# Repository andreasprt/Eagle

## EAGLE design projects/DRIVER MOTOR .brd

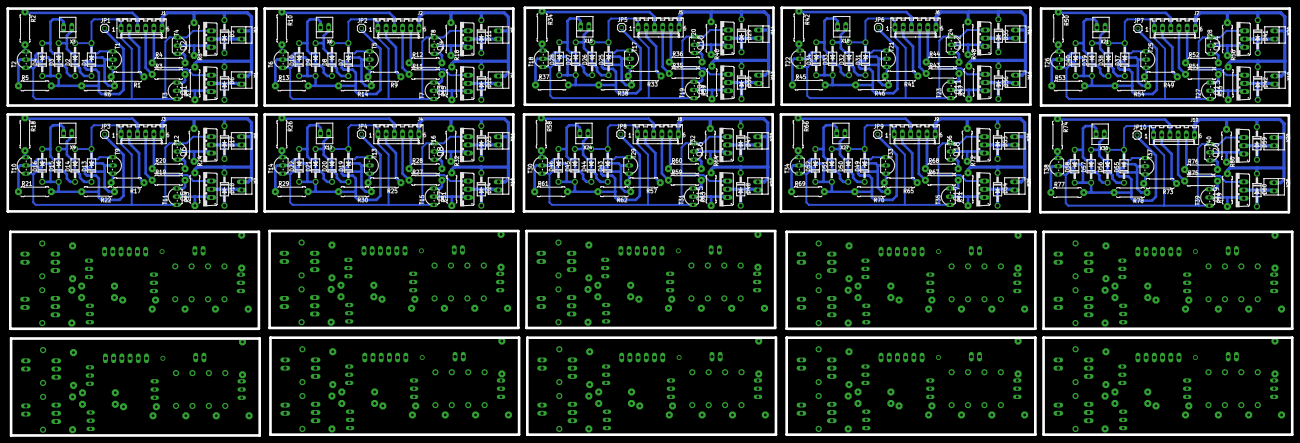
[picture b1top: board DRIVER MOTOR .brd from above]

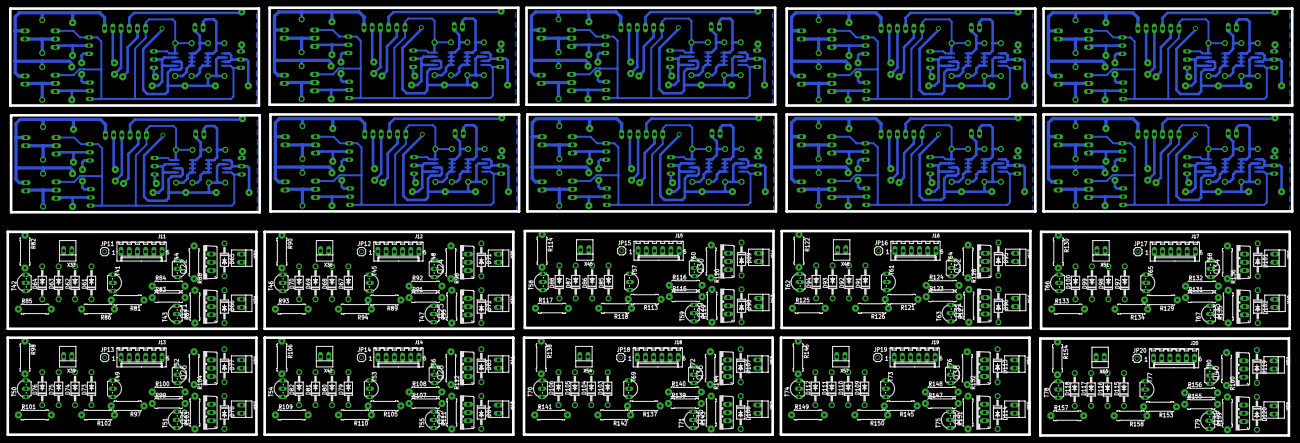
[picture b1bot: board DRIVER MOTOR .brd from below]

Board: 2 copper layers, 397.5 x 132.4 mm, 520 parts (270 on the bottom side), 190 nets.

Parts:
D1, D2, D3, D4, D5, D6, D7, D8, D9, D10, D11, D12, D13, D14, D15, D16, D17, D18, D19, D20, D21, D22, D23, D24, D25, D26, D27, D28, D29, D30, D31, D32, D33, D34, D35, D36, D37, D38, D39, D40, D41, D42, D43, D44, D45, D46, D47, D48, D49, D50, D51, D52, D53, D54, D55, D56, D57, D58, D59, D60, D61, D62, D63, D64, D65, D66, D67, D68, D69, D70, D71, D72, D73, D74, D75, D76, D77, D78, D79, D80, D81, D82, D83, D84, D85, D86, D87, D88, D89, D90, D91, D92, D93, D94, D95, D96, D97, D98, D99, D100, D101, D102, D103, D104, D105, D106, D107, D108, D109, D110, D111, D112, D113, D114, D115, D116, D117, D118, D119, D120: 1N4004; DO41-10
IC1, IC2, IC3, IC4, IC5, IC6, IC7, IC8, IC9, IC10, IC11, IC12, IC13, IC14, IC15, IC16, IC17, IC18, IC19, IC20: LM555D; SO08
J1, J2, J3, J4, J5, J6, J7, J8, J9, J10, J11, J12, J13, J14, J15, J16, J17, J18, J19, J20: 22-27-2061-06; 6410-06
JP1, JP2, JP3, JP4, JP5, JP6, JP7, JP8, JP9, JP10, JP11, JP12, JP13, JP14, JP15, JP16, JP17, JP18, JP19, JP20: 1X01
Q1, Q2, Q3, Q4, Q5, Q6, Q7, Q8, Q9, Q10, Q11, Q12, Q13, Q14, Q15, Q16, Q17, Q18, Q19, Q20, Q21, Q22, Q23, Q24, Q25, Q26, Q27, Q28, Q29, Q30, Q31, Q32, Q33, Q34, Q35, Q36, Q37, Q38, Q39, Q40: IRF530; TO220BV
R1, R2, R3, R4, R9, R10, R11, R12, R17, R18, R19, R20, R25, R26, R27, R28, R33, R34, R35, R36, R41, R42, R43, R44, R49, R50, R51, R52, R57, R58, R59, R60, R65, R66, R67, R68, R73, R74, R75, R76, R81, R82, R83, R84, R89, R90, R91, R92, R97, R98, R99, R100, R105, R106, R107, R108, R113, R114, R115, R116, R121, R122, R123, R124, R129, R130, R131, R132, R137, R138, R139, R140, R145, R146, R147, R148, R153, R154, R155, R156: 150K; 0309/10
R5, R6, R13, R14, R21, R22, R29, R30, R37, R38, R45, R46, R53, R54, R61, R62, R69, R70, R77, R78, R85, R86, R93, R94, R101, R102, R109, R110, R117, R118, R125, R126, R133, R134, R141, R142, R149, R150, R157, R158: 68K; 0309/10
R7, R8, R15, R16, R23, R24, R31, R32, R39, R40, R47, R48, R55, R56, R63, R64, R71, R72, R79, R80, R87, R88, R95, R96, R103, R104, R111, R112, R119, R120, R127, R128, R135, R136, R143, R144, R151, R152, R159, R160: 47K; 0309/10
T1, T2, T3, T4, T5, T6, T7, T8, T9, T10, T11, T12, T13, T14, T15, T16, T17, T18, T19, T20, T21, T22, T23, T24, T25, T26, T27, T28, T29, T30, T31, T32, T33, T34, T35, T36, T37, T38, T39, T40, T41, T42, T43, T44, T45, T46, T47, T48, T49, T50, T51, T52, T53, T54, T55, T56, T57, T58, T59, T60, T61, T62, T63, T64, T65, T66, T67, T68, T69, T70, T71, T72, T73, T74, T75, T76, T77, T78, T79, T80: 2SC945; TO92-ECB
X1, X2, X3, X4, X5, X6, X7, X8, X9, X10, X11, X12, X13, X14, X15, X16, X17, X18, X19, X20, X21, X22, X23, X24, X25, X26, X27, X28, X29, X30, X31, X32, X33, X34, X35, X36, X37, X38, X39, X40, X41, X42, X43, X44, X45, X46, X47, X48, X49, X50, X51, X52, X53, X54, X55, X56, X57, X58, X59, X60: 22-23-2021

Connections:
+12V: D3.C, D4.C, IC1.3, IC2.3, JP1.1, R5.2, R6.2
+12V1: D9.C, D10.C, IC3.3, IC4.3, JP2.1, R13.2, R14.2
+12V2: D15.C, D16.C, IC5.3, IC6.3, JP3.1, R21.2, R22.2
+12V3: D21.C, D22.C, IC7.3, IC8.3, JP4.1, R29.2, R30.2
+12V4: D27.C, D28.C, IC9.3, IC10.3, JP5.1, R37.2, R38.2
+12V5: D33.C, D34.C, IC11.3, IC12.3, JP6.1, R45.2, R46.2
+12V6: D39.C, D40.C, IC13.3, IC14.3, JP7.1, R53.2, R54.2
+12V7: D45.C, D46.C, IC15.3, IC16.3, JP8.1, R61.2, R62.2
+12V8: D51.C, D52.C, IC17.3, IC18.3, JP9.1, R69.2, R70.2
+12V9: D57.C, D58.C, IC19.3, IC20.3, JP10.1, R77.2, R78.2
GND: D1.A, D2.A, IC1.1, IC2.1, J1.1, Q1.S, Q2.S, T1.E, T2.E, T3.E, T4.E
GND1: D7.A, D8.A, IC3.1, IC4.1, J2.1, Q3.S, Q4.S, T5.E, T6.E, T7.E, T8.E
GND2: D13.A, D14.A, IC5.1, IC6.1, J3.1, Q5.S, Q6.S, T9.E, T10.E, T11.E, T12.E
GND3: D19.A, D20.A, IC7.1, IC8.1, J4.1, Q7.S, Q8.S, T13.E, T14.E, T15.E, T16.E
GND4: D25.A, D26.A, IC9.1, IC10.1, J5.1, Q9.S, Q10.S, T17.E, T18.E, T19.E, T20.E
GND5: D31.A, D32.A, IC11.1, IC12.1, J6.1, Q11.S, Q12.S, T21.E, T22.E, T23.E, T24.E
GND6: D37.A, D38.A, IC13.1, IC14.1, J7.1, Q13.S, Q14.S, T25.E, T26.E, T27.E, T28.E
GND7: D43.A, D44.A, IC15.1, IC16.1, J8.1, Q15.S, Q16.S, T29.E, T30.E, T31.E, T32.E
GND8: D49.A, D50.A, IC17.1, IC18.1, J9.1, Q17.S, Q18.S, T33.E, T34.E, T35.E, T36.E
GND9: D55.A, D56.A, IC19.1, IC20.1, J10.1, Q19.S, Q20.S, T37.E, T38.E, T39.E, T40.E
M1: J1.4, R3.1
M2: J1.5, R4.1
M3: J2.4, R11.1
M4: J2.5, R12.1
M5: J3.4, R19.1
M6: J3.5, R20.1
M7: J4.4, R27.1
M8: J4.5, R28.1
M9: J5.4, R35.1
M10: J5.5, R36.1
M11: J6.4, R43.1
M12: J6.5, R44.1
M13: J7.4, R51.1
M14: J7.5, R52.1
M15: J8.4, R59.1
M16: J8.5, R60.1
M17: J9.4, R67.1
M18: J9.5, R68.1
M19: J10.4, R75.1
M20: J10.5, R76.1
unnamed: R1.2, T1.B
unnamed: R2.2, T2.B
unnamed: IC2.2, IC2.4, R5.1, T2.C
unnamed: IC1.2, IC1.4, R6.1, T1.C
unnamed: R3.2, T3.B
unnamed: D1.C, D3.A, IC1.5, IC1.6, IC1.7, IC1.8, X3.1
unnamed: D2.C, D4.A, IC2.5, IC2.6, IC2.7, IC2.8, X3.2
unnamed: R4.2, T4.B
unnamed: Q1.G, R7.1, T3.C
unnamed: Q2.G, R8.1, T4.C
unnamed: D6.A, Q1.D, X1.2
unnamed: R9.2, T5.B
unnamed: D5.A, Q2.D, X2.2
unnamed: R10.2, T6.B
unnamed: IC4.2, IC4.4, R13.1, T6.C
unnamed: J1.2, R1.1
unnamed: J1.3, R2.1
unnamed: IC3.2, IC3.4, R14.1, T5.C
unnamed: D7.C, D9.A, IC3.5, IC3.6, IC3.7, IC3.8, X6.1
unnamed: D8.C, D10.A, IC4.5, IC4.6, IC4.7, IC4.8, X6.2
unnamed: R11.2, T7.B
unnamed: R12.2, T8.B
unnamed: Q3.G, R15.1, T7.C
unnamed: Q4.G, R16.1, T8.C
unnamed: D12.A, Q3.D, X4.2
unnamed: D11.A, Q4.D, X5.2
unnamed: J2.2, R9.1
unnamed: J2.3, R10.1
unnamed: R17.2, T9.B
unnamed: R18.2, T10.B
unnamed: IC6.2, IC6.4, R21.1, T10.C
unnamed: IC5.2, IC5.4, R22.1, T9.C
unnamed: D13.C, D15.A, IC5.5, IC5.6, IC5.7, IC5.8, X9.1
unnamed: D14.C, D16.A, IC6.5, IC6.6, IC6.7, IC6.8, X9.2
unnamed: R19.2, T11.B
unnamed: R20.2, T12.B
unnamed: Q5.G, R23.1, T11.C
unnamed: Q6.G, R24.1, T12.C
unnamed: D18.A, Q5.D, X7.2
unnamed: D17.A, Q6.D, X8.2
unnamed: J3.2, R17.1
unnamed: J3.3, R18.1
unnamed: R25.2, T13.B
unnamed: R26.2, T14.B
unnamed: IC8.2, IC8.4, R29.1, T14.C
unnamed: IC7.2, IC7.4, R30.1, T13.C
unnamed: D19.C, D21.A, IC7.5, IC7.6, IC7.7, IC7.8, X12.1
unnamed: D20.C, D22.A, IC8.5, IC8.6, IC8.7, IC8.8, X12.2
unnamed: R27.2, T15.B
unnamed: R28.2, T16.B
unnamed: Q7.G, R31.1, T15.C
unnamed: Q8.G, R32.1, T16.C
unnamed: D24.A, Q7.D, X10.2
unnamed: D23.A, Q8.D, X11.2
unnamed: J4.2, R25.1
unnamed: J4.3, R26.1
unnamed: R33.2, T17.B
unnamed: R34.2, T18.B
unnamed: IC10.2, IC10.4, R37.1, T18.C
unnamed: IC9.2, IC9.4, R38.1, T17.C
unnamed: D25.C, D27.A, IC9.5, IC9.6, IC9.7, IC9.8, X15.1
unnamed: D26.C, D28.A, IC10.5, IC10.6, IC10.7, IC10.8, X15.2
unnamed: R35.2, T19.B
unnamed: R36.2, T20.B
unnamed: Q9.G, R39.1, T19.C
unnamed: Q10.G, R40.1, T20.C
unnamed: D30.A, Q9.D, X13.2
unnamed: D29.A, Q10.D, X14.2
unnamed: J5.2, R33.1
unnamed: J5.3, R34.1
unnamed: R41.2, T21.B
unnamed: R42.2, T22.B
unnamed: IC12.2, IC12.4, R45.1, T22.C
unnamed: IC11.2, IC11.4, R46.1, T21.C
unnamed: D31.C, D33.A, IC11.5, IC11.6, IC11.7, IC11.8, X18.1
unnamed: D32.C, D34.A, IC12.5, IC12.6, IC12.7, IC12.8, X18.2
unnamed: R43.2, T23.B
unnamed: R44.2, T24.B
unnamed: Q11.G, R47.1, T23.C
unnamed: Q12.G, R48.1, T24.C
unnamed: D36.A, Q11.D, X16.2
unnamed: D35.A, Q12.D, X17.2
unnamed: J6.2, R41.1
unnamed: J6.3, R42.1
unnamed: R49.2, T25.B
unnamed: R50.2, T26.B
unnamed: IC14.2, IC14.4, R53.1, T26.C
unnamed: IC13.2, IC13.4, R54.1, T25.C
unnamed: D37.C, D39.A, IC13.5, IC13.6, IC13.7, IC13.8, X21.1
unnamed: D38.C, D40.A, IC14.5, IC14.6, IC14.7, IC14.8, X21.2
unnamed: R51.2, T27.B
unnamed: R52.2, T28.B
unnamed: Q13.G, R55.1, T27.C
unnamed: Q14.G, R56.1, T28.C
unnamed: D42.A, Q13.D, X19.2
unnamed: D41.A, Q14.D, X20.2
unnamed: J7.2, R49.1
unnamed: J7.3, R50.1
unnamed: R57.2, T29.B
unnamed: R58.2, T30.B
unnamed: IC16.2, IC16.4, R61.1, T30.C
unnamed: IC15.2, IC15.4, R62.1, T29.C
unnamed: D43.C, D45.A, IC15.5, IC15.6, IC15.7, IC15.8, X24.1
unnamed: D44.C, D46.A, IC16.5, IC16.6, IC16.7, IC16.8, X24.2
unnamed: R59.2, T31.B
unnamed: R60.2, T32.B
unnamed: Q15.G, R63.1, T31.C
unnamed: Q16.G, R64.1, T32.C
unnamed: D48.A, Q15.D, X22.2
unnamed: D47.A, Q16.D, X23.2
unnamed: J8.2, R57.1
unnamed: J8.3, R58.1
unnamed: R65.2, T33.B
unnamed: R66.2, T34.B
unnamed: IC18.2, IC18.4, R69.1, T34.C
unnamed: IC17.2, IC17.4, R70.1, T33.C
unnamed: D49.C, D51.A, IC17.5, IC17.6, IC17.7, IC17.8, X27.1
unnamed: D50.C, D52.A, IC18.5, IC18.6, IC18.7, IC18.8, X27.2
unnamed: R67.2, T35.B
unnamed: R68.2, T36.B
unnamed: Q17.G, R71.1, T35.C
unnamed: Q18.G, R72.1, T36.C
unnamed: D54.A, Q17.D, X25.2
unnamed: D53.A, Q18.D, X26.2
unnamed: J9.2, R65.1
unnamed: J9.3, R66.1
unnamed: R73.2, T37.B
unnamed: R74.2, T38.B
unnamed: IC20.2, IC20.4, R77.1, T38.C
unnamed: IC19.2, IC19.4, R78.1, T37.C
unnamed: D55.C, D57.A, IC19.5, IC19.6, IC19.7, IC19.8, X30.1
unnamed: D56.C, D58.A, IC20.5, IC20.6, IC20.7, IC20.8, X30.2
unnamed: R75.2, T39.B
unnamed: R76.2, T40.B
unnamed: Q19.G, R79.1, T39.C
unnamed: Q20.G, R80.1, T40.C
unnamed: D60.A, Q19.D, X28.2
unnamed: D59.A, Q20.D, X29.2
unnamed: J10.2, R73.1
unnamed: J10.3, R74.1
VCC: D5.C, D6.C, J1.6, R7.2, R8.2, X1.1, X2.1
VCC1: D11.C, D12.C, J2.6, R15.2, R16.2, X4.1, X5.1
VCC2: D17.C, D18.C, J3.6, R23.2, R24.2, X7.1, X8.1
VCC3: D23.C, D24.C, J4.6, R31.2, R32.2, X10.1, X11.1
VCC4: D29.C, D30.C, J5.6, R39.2, R40.2, X13.1, X14.1
VCC5: D35.C, D36.C, J6.6, R47.2, R48.2, X16.1, X17.1
VCC6: D41.C, D42.C, J7.6, R55.2, R56.2, X19.1, X20.1
VCC7: D47.C, D48.C, J8.6, R63.2, R64.2, X22.1, X23.1
VCC8: D53.C, D54.C, J9.6, R71.2, R72.2, X25.1, X26.1
VCC9: D59.C, D60.C, J10.6, R79.2, R80.2, X28.1, X29.1

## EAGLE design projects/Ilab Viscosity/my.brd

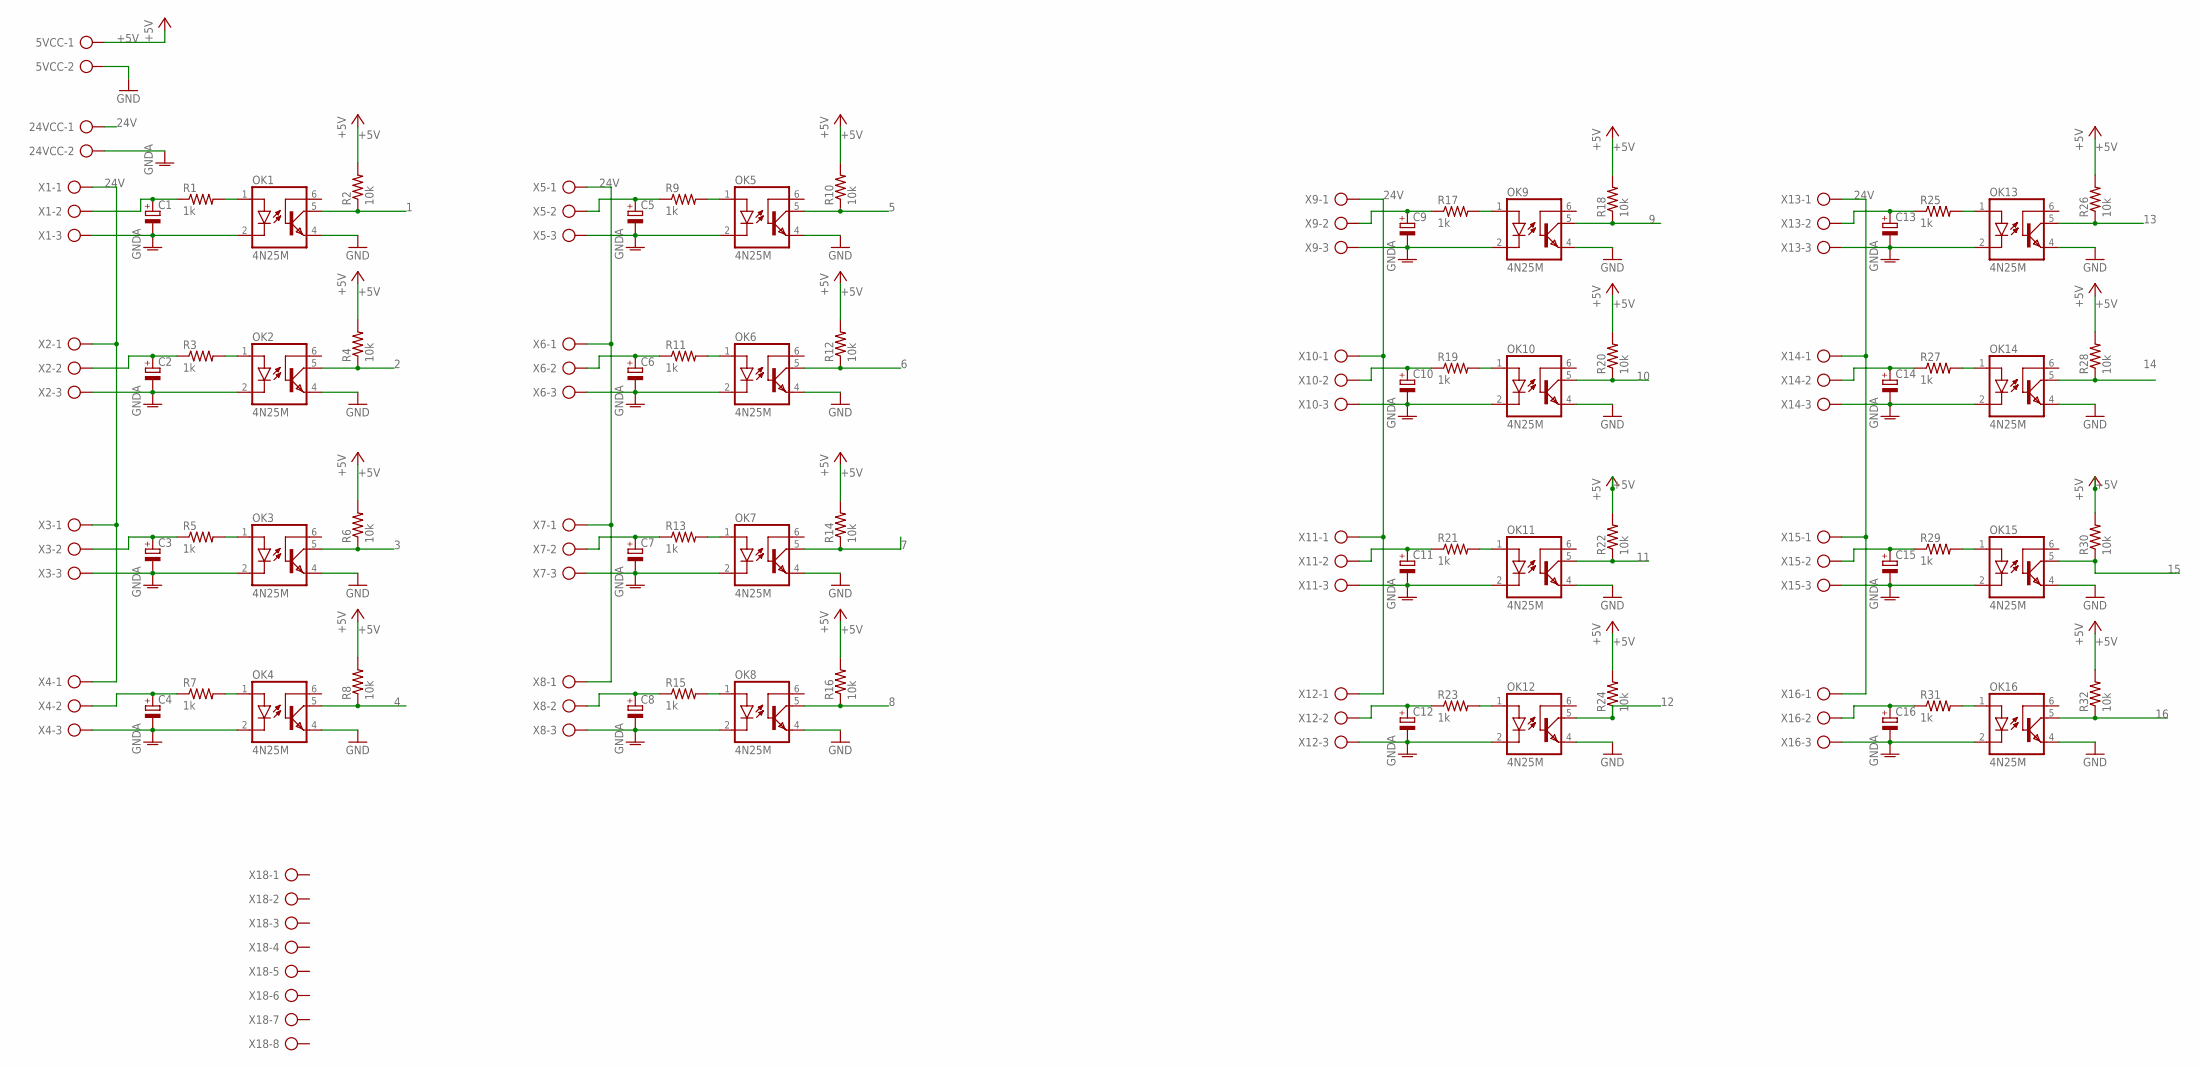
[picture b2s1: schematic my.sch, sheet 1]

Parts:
5VCC, 24VCC: AK300/2
C1, C2, C3, C4, C5, C6, C7, C8, C9, C10, C11, C12, C13, C14, C15, C16: CPOL-EUE2.5-5; E2,5-5
OK1, OK2, OK3, OK4, OK5, OK6, OK7, OK8, OK9, OK10, OK11, OK12, OK13, OK14, OK15, OK16: 4N25M; DIL06
R1, R3, R5, R7, R9, R11, R13, R15, R17, R19, R21, R23, R25, R27, R29, R31: 1k; 0207/10
R2, R4, R6, R8, R10, R12, R14, R16, R18, R20, R22, R24, R26, R28, R30, R32: 10k; 0207/10
X1, X2, X3, X4, X5, X6, X7, X8, X9, X10, X11, X12, X13, X14, X15, X16: AK300/3
X18: AK300/8

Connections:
1: OK1.5 (COL), R2.1; also elsewhere on the board
2: OK2.5 (COL), R4.1; also elsewhere on the board
3: OK3.5 (COL), R6.1; also elsewhere on the board
4: OK4.5 (COL), R8.1; also elsewhere on the board
5: OK5.5 (COL), R10.1; also elsewhere on the board
6: OK6.5 (COL), R12.1; also elsewhere on the board
7: OK7.5 (COL), R14.1; also elsewhere on the board
8: OK8.5 (COL), R16.1; also elsewhere on the board
9: OK9.5 (COL), R18.1; also elsewhere on the board
10: OK10.5 (COL), R20.1; also elsewhere on the board
11: OK11.5 (COL), R22.1; also elsewhere on the board
12: OK12.5 (COL), R24.1; also elsewhere on the board
13: OK13.5 (COL), R26.1; also elsewhere on the board
14: OK14.5 (COL), R28.1; also elsewhere on the board
15: OK15.5 (COL), R30.1; also elsewhere on the board
16: OK16.5 (COL), R32.1; also elsewhere on the board
24V: 24VCC.1, X1.1, X2.1, X3.1, X4.1, X5.1, X6.1, X7.1, X8.1, X9.1, X10.1, X11.1, X12.1, X13.1, X14.1, X15.1, X16.1
+5V: 5VCC.1, R2.2, R4.2, R6.2, R8.2, R10.2, R12.2, R14.2, R16.2, R18.2, R20.2, R22.2, R24.2, R26.2, R28.2, R30.2, R32.2; also elsewhere on the board
GND: 5VCC.2, OK1.4 (EMI), OK2.4 (EMI), OK3.4 (EMI), OK4.4 (EMI), OK5.4 (EMI), OK6.4 (EMI), OK7.4 (EMI), OK8.4 (EMI), OK9.4 (EMI), OK10.4 (EMI), OK11.4 (EMI), OK12.4 (EMI), OK13.4 (EMI), OK14.4 (EMI), OK15.4 (EMI), OK16.4 (EMI); also elsewhere on the board
GNDA: 24VCC.2, C1.-, C2.-, C3.-, C4.-, C5.-, C6.-, C7.-, C8.-, C9.-, C10.-, C11.-, C12.-, C13.-, C14.-, C15.-, C16.-, OK1.2 (C), OK2.2 (C), OK3.2 (C), OK4.2 (C), OK5.2 (C), OK6.2 (C), OK7.2 (C), OK8.2 (C), OK9.2 (C), OK10.2 (C), OK11.2 (C), OK12.2 (C), OK13.2 (C), OK14.2 (C), OK15.2 (C), OK16.2 (C), X1.3, X2.3, X3.3, X4.3, X5.3, X6.3, X7.3, X8.3, X9.3, X10.3, X11.3, X12.3, X13.3, X14.3, X15.3, X16.3
unnamed: OK1.1 (A), R1.2
unnamed: OK2.1 (A), R3.2
unnamed: C2.+, R3.1, X2.2
unnamed: OK3.1 (A), R5.2
unnamed: C3.+, R5.1, X3.2
unnamed: OK4.1 (A), R7.2
unnamed: C4.+, R7.1, X4.2
unnamed: OK5.1 (A), R9.2
unnamed: C5.+, R9.1, X5.2
unnamed: OK6.1 (A), R11.2
unnamed: C1.+, R1.1, X1.2
unnamed: C6.+, R11.1, X6.2
unnamed: OK7.1 (A), R13.2
unnamed: C7.+, R13.1, X7.2
unnamed: OK8.1 (A), R15.2
unnamed: C8.+, R15.1, X8.2
unnamed: OK9.1 (A), R17.2
unnamed: C9.+, R17.1, X9.2
unnamed: OK10.1 (A), R19.2
unnamed: C10.+, R19.1, X10.2
unnamed: OK11.1 (A), R21.2
unnamed: C11.+, R21.1, X11.2
unnamed: OK12.1 (A), R23.2
unnamed: C12.+, R23.1, X12.2
unnamed: OK13.1 (A), R25.2
unnamed: C13.+, R25.1, X13.2
unnamed: OK14.1 (A), R27.2
unnamed: C14.+, R27.1, X14.2
unnamed: OK15.1 (A), R29.2
unnamed: C15.+, R29.1, X15.2
unnamed: OK16.1 (A), R31.2
unnamed: C16.+, R31.1, X16.2

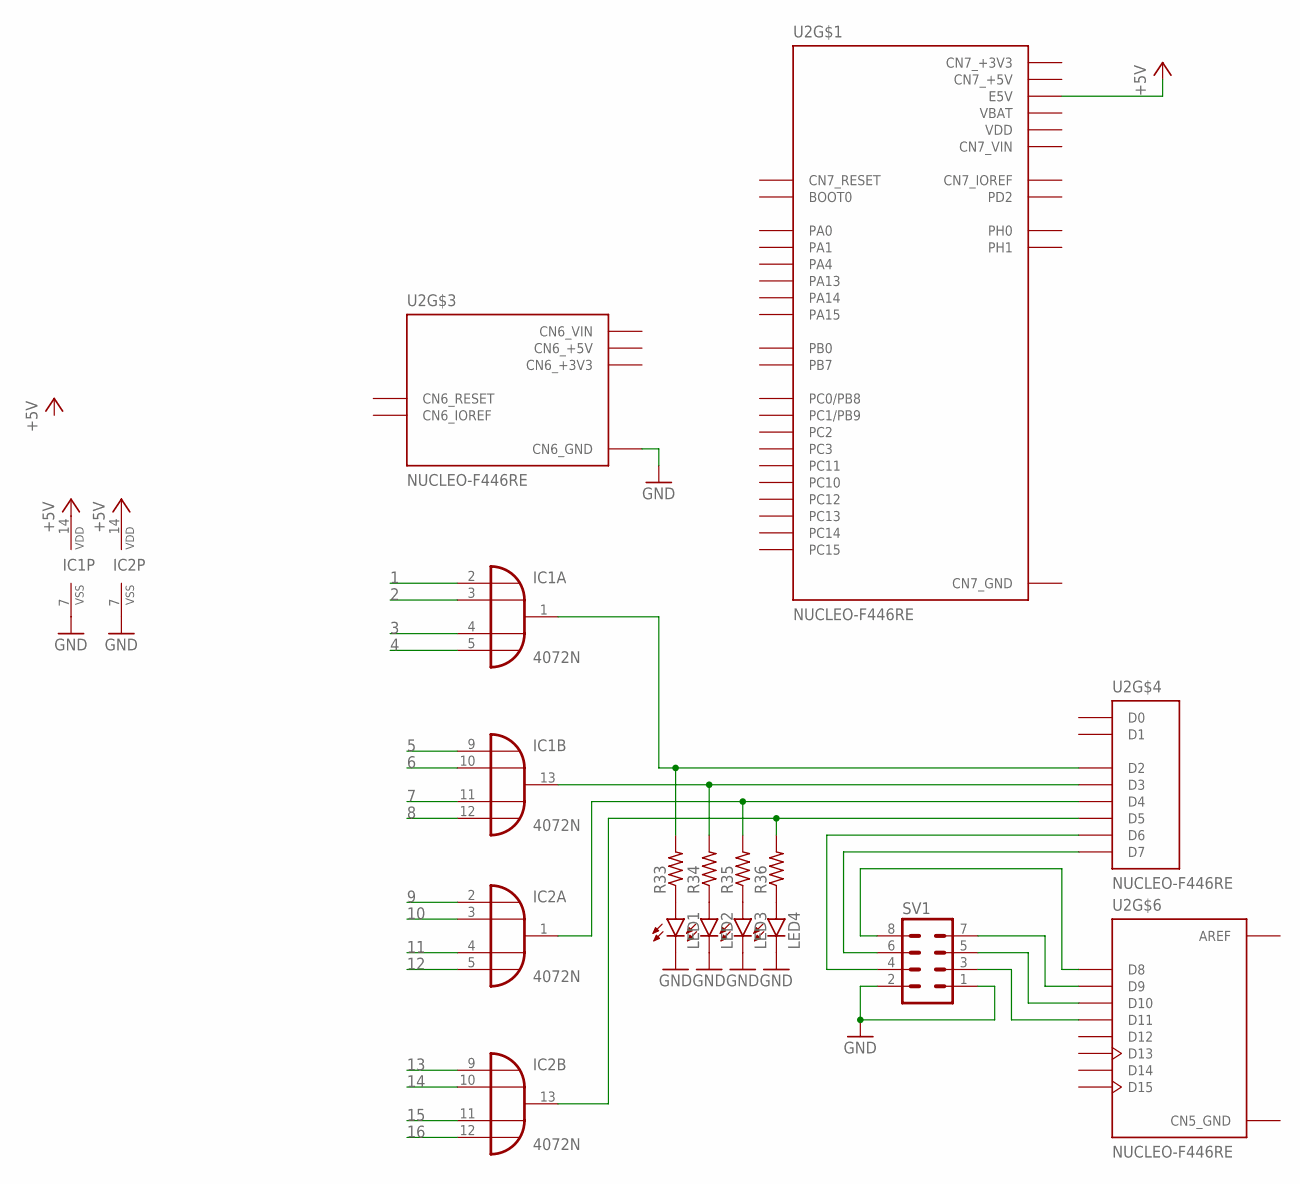
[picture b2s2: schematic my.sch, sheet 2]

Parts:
IC1, IC2: 4072N; DIL14
LED1, LED2, LED3, LED4: LED3MM
R33, R34, R35, R36: R-US_0207/10; 0207/10
SV1: MA04-2
U2: NUCLEO-F446RE; MODULE_NUCLEO-F446RE

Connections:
1: IC1.2 (I0); also elsewhere on the board
2: IC1.3 (I1); also elsewhere on the board
3: IC1.4 (I2); also elsewhere on the board
4: IC1.5 (I3); also elsewhere on the board
5: IC1.9 (I0); also elsewhere on the board
6: IC1.10 (I1); also elsewhere on the board
7: IC1.11 (I2); also elsewhere on the board
8: IC1.12 (I3); also elsewhere on the board
9: IC2.2 (I0); also elsewhere on the board
10: IC2.3 (I1); also elsewhere on the board
11: IC2.4 (I2); also elsewhere on the board
12: IC2.5 (I3); also elsewhere on the board
13: IC2.9 (I0); also elsewhere on the board
14: IC2.10 (I1); also elsewhere on the board
15: IC2.11 (I2); also elsewhere on the board
16: IC2.12 (I3); also elsewhere on the board
+5V: IC1.14 (VDD), IC2.14 (VDD), U2.CN7_6 (E5V); also elsewhere on the board
AGND: U2.CN10_32 (AGND)
AREF: U2.CN5_8 (AREF)
AVDD: U2.CN10_7 (AVDD)
CN5_GND: U2.CN5_7 (CN5_GND)
CN6_+3V3: U2.CN6_4 (CN6_+3V3)
CN6_+5V: U2.CN6_5 (CN6_+5V)
CN6_VIN: U2.CN6_8 (CN6_VIN)
CN7_+3V3: U2.CN7_16 (CN7_+3V3)
CN7_+5V: U2.CN7_18 (CN7_+5V)
CN7_GND: U2.CN7_8 (CN7_GND), U2.CN7_19 (CN7_GND), U2.CN7_20 (CN7_GND), U2.CN7_22 (CN7_GND)
CN7_VIN: U2.CN7_24 (CN7_VIN)
CN10_GND: U2.CN10_9 (CN10_GND), U2.CN10_20 (CN10_GND)
GND: IC1.7 (VSS), IC2.7 (VSS), LED1.K (C), LED2.K (C), LED3.K (C), LED4.K (C), SV1.1, SV1.2, U2.CN6_6 (CN6_GND), U2.CN6_7 (CN6_GND); also elsewhere on the board
unnamed: IC1.1 (O), R33.2, U2.CN9_3 (D2)
unnamed: IC1.13 (O), R34.2, U2.CN9_4 (D3)
unnamed: IC2.1 (O), R35.2, U2.CN9_5 (D4)
unnamed: IC2.13 (O), R36.2, U2.CN9_6 (D5)
unnamed: SV1.3, U2.CN5_4 (D11)
unnamed: SV1.4, U2.CN9_7 (D6)
unnamed: SV1.6, U2.CN9_8 (D7)
unnamed: SV1.8, U2.CN5_1 (D8)
unnamed: SV1.7, U2.CN5_2 (D9)
unnamed: SV1.5, U2.CN5_3 (D10)
unnamed: LED1.A, R33.1
unnamed: LED2.A, R34.1
unnamed: LED3.A, R35.1
unnamed: LED4.A, R36.1
U5V: U2.CN10_8 (U5V)
VBAT: U2.CN7_33 (VBAT)
VDD: U2.CN7_5 (VDD)

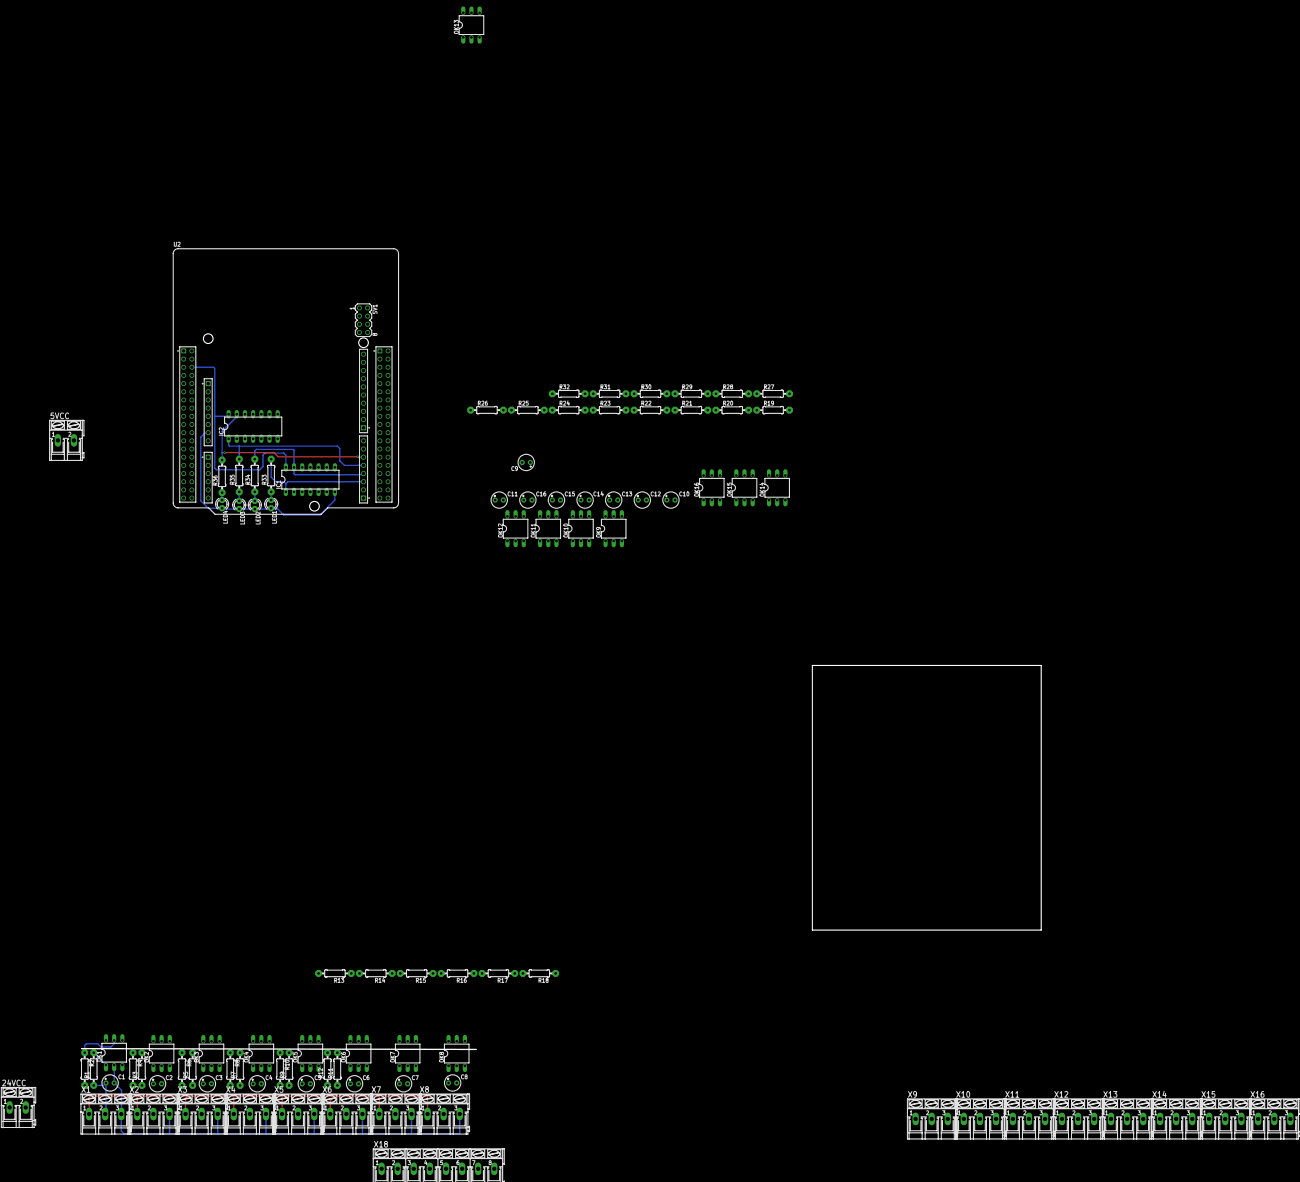
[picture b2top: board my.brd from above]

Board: 2 copper layers, 95 parts (0 on the bottom side), 68 nets.

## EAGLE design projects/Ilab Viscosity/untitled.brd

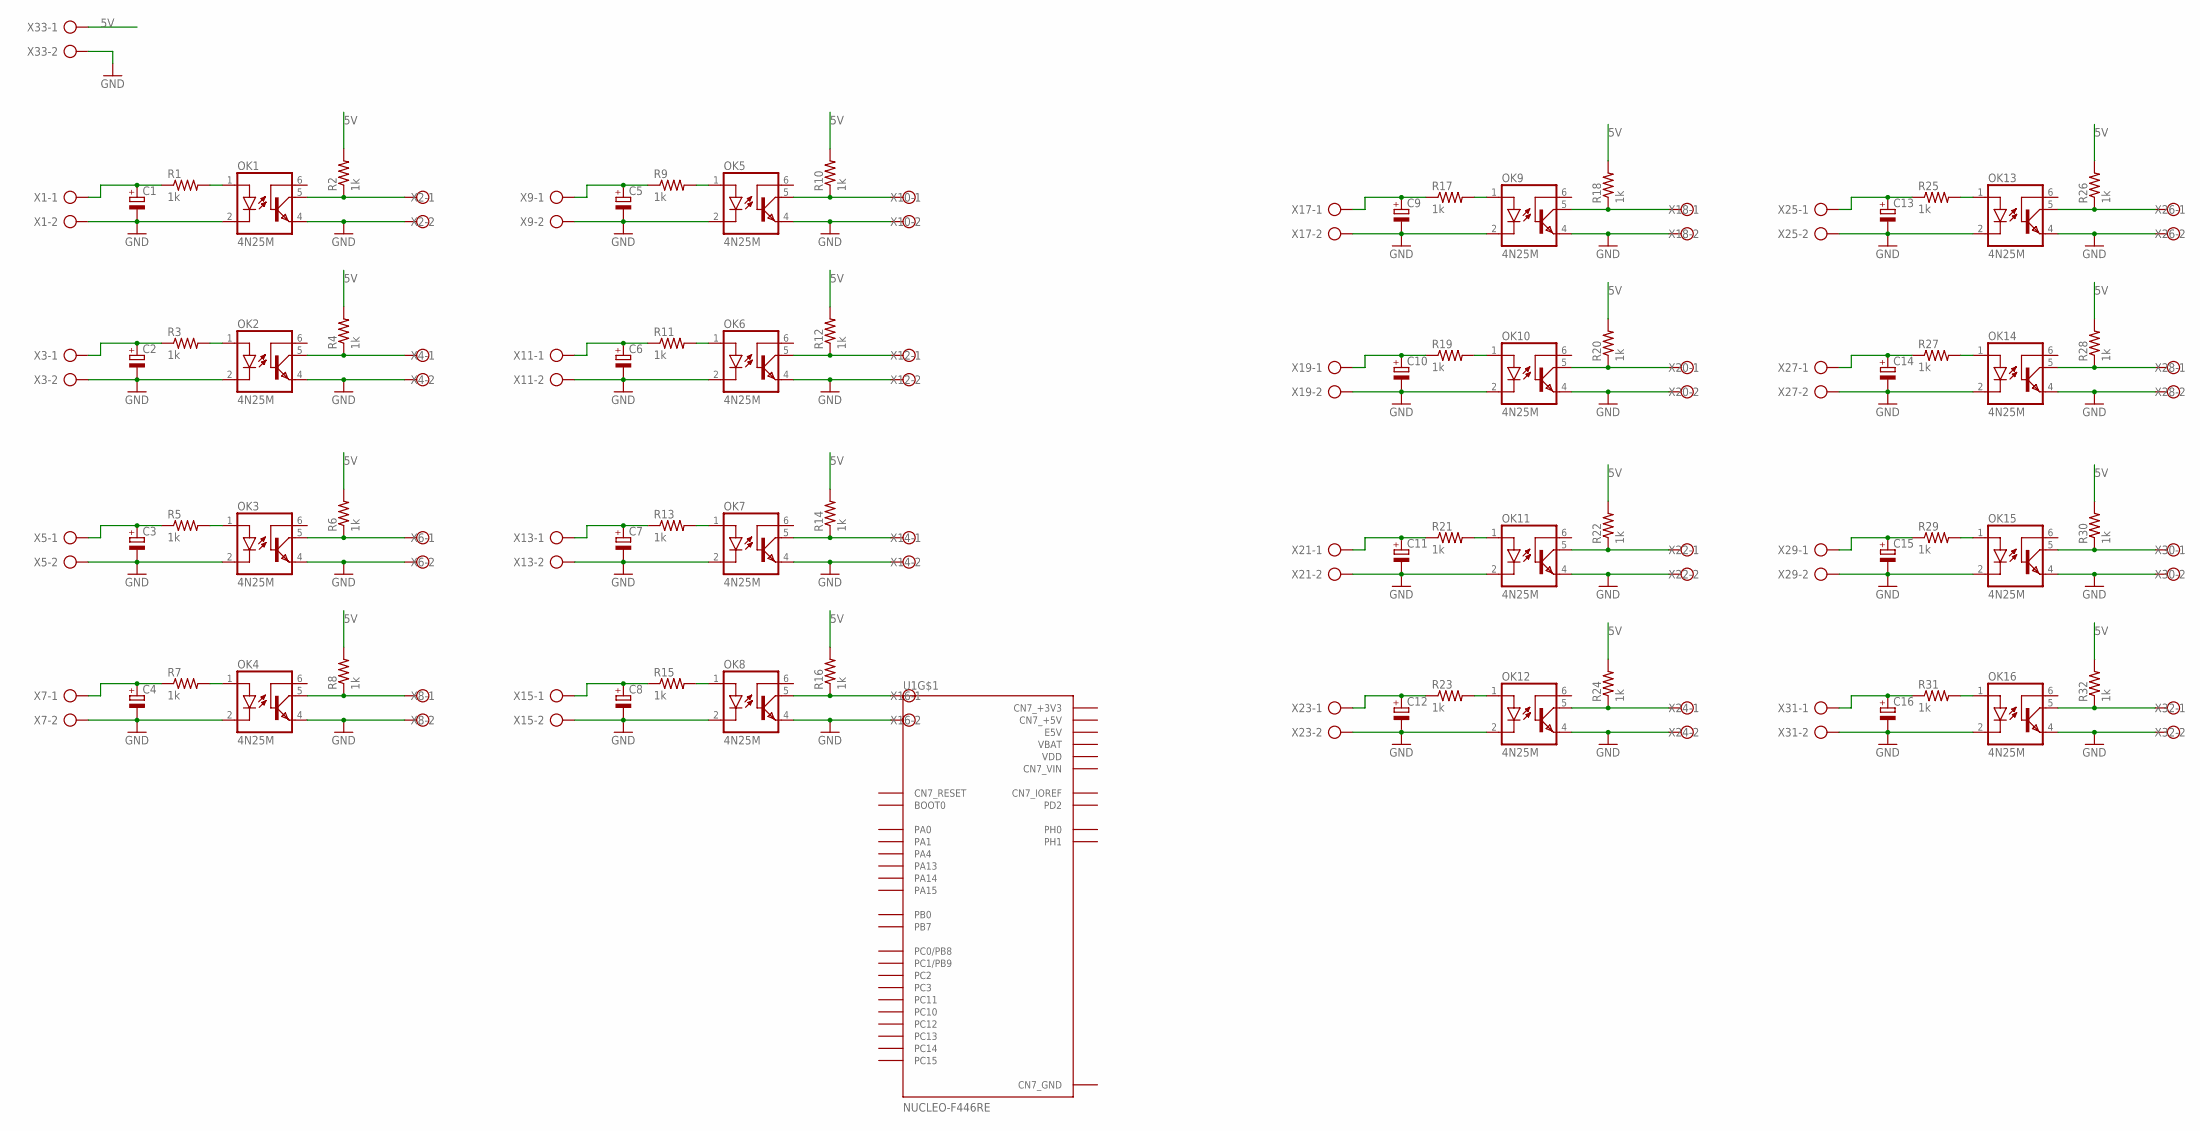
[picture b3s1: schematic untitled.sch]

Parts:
C1, C2, C3, C4, C5, C6, C7, C8, C9, C10, C11, C12, C13, C14, C15, C16: CPOL-EUE2.5-5; E2,5-5
OK1, OK2, OK3, OK4, OK5, OK6, OK7, OK8, OK9, OK10, OK11, OK12, OK13, OK14, OK15, OK16: 4N25M; DIL06
R1, R2, R3, R4, R5, R6, R7, R8, R9, R10, R11, R12, R13, R14, R15, R16, R17, R18, R19, R20, R21, R22, R23, R24, R25, R26, R27, R28, R29, R30, R31, R32: 1k; 0207/10
U1: NUCLEO-F446RE; MODULE_NUCLEO-F446RE
X1, X2, X3, X4, X5, X6, X7, X8, X9, X10, X11, X12, X13, X14, X15, X16, X17, X18, X19, X20, X21, X22, X23, X24, X25, X26, X27, X28, X29, X30, X31, X32, X33: AK300/2

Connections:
5V: R2.2, R4.2, R6.2, R8.2, R10.2, R12.2, R14.2, R16.2, R18.2, R20.2, R22.2, R24.2, R26.2, R28.2, R30.2, R32.2, X33.1
AGND: U1.CN10_32 (AGND)
AREF: U1.CN5_8 (AREF)
AVDD: U1.CN10_7 (AVDD)
CN5_GND: U1.CN5_7 (CN5_GND)
CN6_+3V3: U1.CN6_4 (CN6_+3V3)
CN6_+5V: U1.CN6_5 (CN6_+5V)
CN6_GND: U1.CN6_6 (CN6_GND), U1.CN6_7 (CN6_GND)
CN6_VIN: U1.CN6_8 (CN6_VIN)
CN7_+3V3: U1.CN7_16 (CN7_+3V3)
CN7_+5V: U1.CN7_18 (CN7_+5V)
CN7_GND: U1.CN7_8 (CN7_GND), U1.CN7_19 (CN7_GND), U1.CN7_20 (CN7_GND), U1.CN7_22 (CN7_GND)
CN7_VIN: U1.CN7_24 (CN7_VIN)
CN10_GND: U1.CN10_9 (CN10_GND), U1.CN10_20 (CN10_GND)
E5V: U1.CN7_6 (E5V)
GND: C1.-, C2.-, C3.-, C4.-, C5.-, C6.-, C7.-, C8.-, C9.-, C10.-, C11.-, C12.-, C13.-, C14.-, C15.-, C16.-, OK1.2 (C), OK1.4 (EMI), OK2.2 (C), OK2.4 (EMI), OK3.2 (C), OK3.4 (EMI), OK4.2 (C), OK4.4 (EMI), OK5.2 (C), OK5.4 (EMI), OK6.2 (C), OK6.4 (EMI), OK7.2 (C), OK7.4 (EMI), OK8.2 (C), OK8.4 (EMI), OK9.2 (C), OK9.4 (EMI), OK10.2 (C), OK10.4 (EMI), OK11.2 (C), OK11.4 (EMI), OK12.2 (C), OK12.4 (EMI), OK13.2 (C), OK13.4 (EMI), OK14.2 (C), OK14.4 (EMI), OK15.2 (C), OK15.4 (EMI), OK16.2 (C), OK16.4 (EMI), X1.2, X2.2, X3.2, X4.2, X5.2, X6.2, X7.2, X8.2, X9.2, X10.2, X11.2, X12.2, X13.2, X14.2, X15.2, X16.2, X17.2, X18.2, X19.2, X20.2, X21.2, X22.2, X23.2, X24.2, X25.2, X26.2, X27.2, X28.2, X29.2, X30.2, X31.2, X32.2, X33.2
unnamed: OK1.1 (A), R1.2
unnamed: OK2.1 (A), R3.2
unnamed: C2.+, R3.1, X3.1
unnamed: OK2.5 (COL), R4.1, X4.1
unnamed: OK3.1 (A), R5.2
unnamed: C3.+, R5.1, X5.1
unnamed: OK3.5 (COL), R6.1, X6.1
unnamed: OK4.1 (A), R7.2
unnamed: C4.+, R7.1, X7.1
unnamed: OK4.5 (COL), R8.1, X8.1
unnamed: OK5.1 (A), R9.2
unnamed: C5.+, R9.1, X9.1
unnamed: OK5.5 (COL), R10.1, X10.1
unnamed: OK6.1 (A), R11.2
unnamed: C1.+, R1.1, X1.1
unnamed: C6.+, R11.1, X11.1
unnamed: OK1.5 (COL), R2.1, X2.1
unnamed: OK6.5 (COL), R12.1, X12.1
unnamed: OK7.1 (A), R13.2
unnamed: C7.+, R13.1, X13.1
unnamed: OK7.5 (COL), R14.1, X14.1
unnamed: OK8.1 (A), R15.2
unnamed: C8.+, R15.1, X15.1
unnamed: OK8.5 (COL), R16.1, X16.1
unnamed: OK9.1 (A), R17.2
unnamed: C9.+, R17.1, X17.1
unnamed: OK9.5 (COL), R18.1, X18.1
unnamed: OK10.1 (A), R19.2
unnamed: C10.+, R19.1, X19.1
unnamed: OK10.5 (COL), R20.1, X20.1
unnamed: OK11.1 (A), R21.2
unnamed: C11.+, R21.1, X21.1
unnamed: OK11.5 (COL), R22.1, X22.1
unnamed: OK12.1 (A), R23.2
unnamed: C12.+, R23.1, X23.1
unnamed: OK12.5 (COL), R24.1, X24.1
unnamed: OK13.1 (A), R25.2
unnamed: C13.+, R25.1, X25.1
unnamed: OK13.5 (COL), R26.1, X26.1
unnamed: OK14.1 (A), R27.2
unnamed: C14.+, R27.1, X27.1
unnamed: OK14.5 (COL), R28.1, X28.1
unnamed: OK15.1 (A), R29.2
unnamed: C15.+, R29.1, X29.1
unnamed: OK15.5 (COL), R30.1, X30.1
unnamed: OK16.1 (A), R31.2
unnamed: C16.+, R31.1, X31.1
unnamed: OK16.5 (COL), R32.1, X32.1
U5V: U1.CN10_8 (U5V)
VBAT: U1.CN7_33 (VBAT)
VDD: U1.CN7_5 (VDD)

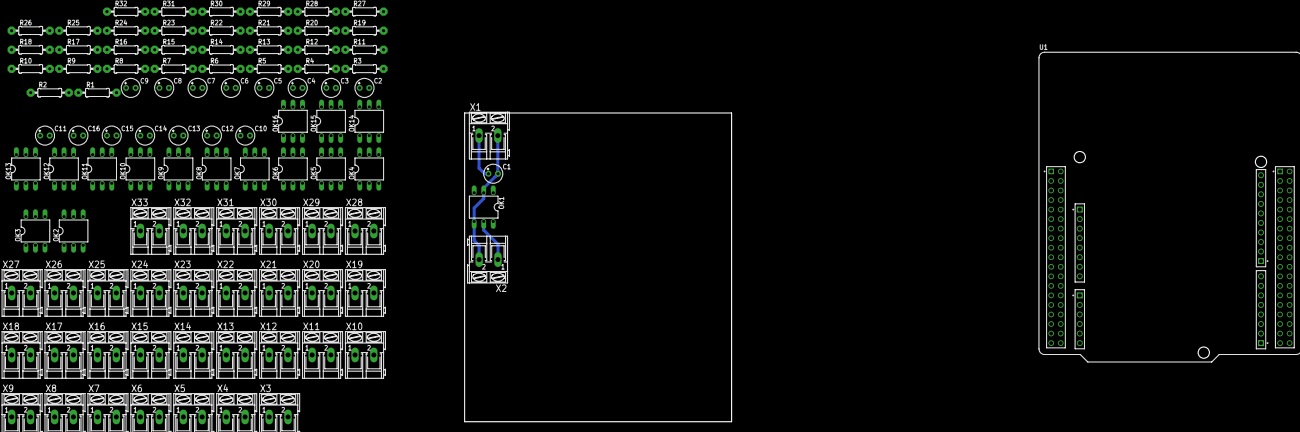
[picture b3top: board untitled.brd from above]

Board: 2 copper layers, 98 parts (0 on the bottom side), 53 nets.

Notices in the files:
parts and their libraries:
SparkFun-Connectors: Licensing: Creative Commons ShareAlike 4.0 International - https://creativecommons.org/licenses/by-sa/4.0
diy-modules: Released under the Creative Commons Attribution 4.0 International License: http://creativecommons.org/licenses/by/4.0
